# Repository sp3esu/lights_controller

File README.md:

# RC Light Controller

Wireless light controller for RC cars and trucks. A touchscreen handheld remote (TX) communicates over ESP-NOW with a receiver (RX) mounted on the vehicle to control multiple light outputs in real time.

## Translations

- [Polski (PL)](docs/README_PL.md)
- [Deutsch (DE)](docs/README_DE.md)
- [Francais (FR)](docs/README_FR.md)
- [Русский (RU)](docs/README_RU.md)
- [Українська (UA)](docs/README_UA.md)

## Features

- **5 independent light channels**: low beam, high beam, fog lights, light bar, hazard lights
- **Touchscreen UI**: 2x3 button grid on a 1.47" color display with LVGL
- **ESP-NOW wireless**: low-latency, connectionless protocol — no WiFi router needed
- **Automatic pairing**: one-button pairing with persistent NVS storage
- **Safety interlocks**: high beam requires low beam; failsafe shuts off all lights after 30s without signal
- **Connection monitoring**: heartbeats, ACK-based command confirmation, NeoPixel status LED
- **Test mode**: controller works standalone for UI testing without a receiver

## Hardware

### Controller (TX)

| Component | Details |
|-----------|---------|
| Board | [Waveshare ESP32-C6-Touch-LCD-1.47-M](https://www.waveshare.com/wiki/ESP32-C6-Touch-LCD-1.47) |
| MCU | ESP32-C6 (RISC-V, 8 MB flash) |
| Display | 1.47" JD9853, 172x320, rotated to 320x172 landscape |
| Touch | AXS5106L capacitive (I2C @ 0x63) |
| Status LED | WS2812 NeoPixel on GPIO8 |

### Receiver (RX)

| Component | Details |
|-----------|---------|
| Board | Any ESP32 dev board (classic Xtensa) |
| Light outputs | 5x GPIO, active-HIGH |
| Status LED | Built-in LED on GPIO2 |
| Pairing | BOOT button (GPIO0) — hold during power-up |

### Receiver Wiring

Connect ESP32 GPIOs to your lights through appropriate drivers (MOSFETs, relays, or LED drivers) depending on voltage and current requirements. All outputs are active-HIGH (3.3 V logic).

| GPIO | Function |
|------|----------|
| 16 | Fog lights |
| 17 | Low beam |
| 18 | High beam |
| 19 | Light bar |
| 21 | Hazard lights |
| 2 | Status LED |
| 0 | Pairing button (BOOT) |

## Building & Flashing

### Prerequisites

- [PlatformIO](https://platformio.org/) (CLI or IDE plugin)
- USB cables for both boards

### Build

```bash
# Build controller (TX) firmware
pio run -e controller

# Build receiver (RX) firmware
pio run -e receiver
```

### Flash

```bash
# Flash controller
pio run -e controller -t upload

# Flash receiver
pio run -e receiver -t upload
```

### Serial Monitor

```bash
pio device monitor    # 115200 baud
```

## Pairing

1. Power on the **receiver** while holding the **BOOT button** (GPIO0). The status LED flashes 3 times to confirm pairing mode.
2. On the **controller**, open **Settings** and tap **Start Pairing**.
3. Both devices exchange MAC addresses over ESP-NOW broadcast and store them in NVS.
4. Power-cycle both devices. The pairing is persistent and survives reboots.

## Protocol

Communication uses ESP-NOW with packed C structs (`__attribute__((packed))`) for cross-architecture compatibility (RISC-V controller / Xtensa receiver).

| Message | Direction | Purpose |
|---------|-----------|---------|
| `LightCommand` | TX -> RX | Set light state (5-bit bitmask) |
| `LightAck` | RX -> TX | Confirm current state |
| `Heartbeat` | RX -> TX | Keep-alive (every 2 s) |
| `StateReport` | RX -> TX | Full state + uptime |
| `PairRequest` | TX -> RX | Broadcast pairing request |
| `PairResponse` | RX -> TX | Pairing response with MAC |

### Light Bitmask

| Bit | Light |
|-----|-------|
| 0 | Fog lights |
| 1 | Low beam |
| 2 | High beam |
| 3 | Light bar |
| 4 | Hazard lights |

### Timing

| Parameter | Value |
|-----------|-------|
| ACK timeout | 200 ms |
| Max retries | 3 |
| Heartbeat interval | 2 s |
| Connection timeout (TX) | 6 s |
| Failsafe timeout (RX) | 30 s |

## Project Structure

```
light_controller/
├── src/
│   ├── controller/      # TX: display, touch, LVGL UI, ESP-NOW TX
│   └── receiver/        # RX: GPIO outputs, ESP-NOW RX, failsafe
├── lib/
│   ├── protocol/        # Shared wire protocol definitions
│   └── axs5106l_touch/  # AXS5106L touch driver
├── include/
│   └── lv_conf.h        # LVGL 8.4 configuration
└── platformio.ini       # Build configuration (two environments)
```

## Dependencies

### Controller
- [LVGL 8.4](https://lvgl.io/) — touchscreen UI framework
- [Arduino_GFX 1.6.5](https://github.com/moononournation/Arduino_GFX) — display driver
- [FastLED 3.9](https://fastled.io/) — NeoPixel status LED

### Receiver
- ESP-IDF built-ins only (ESP-NOW, WiFi, Preferences)

## License

This project is open source. See [LICENSE](LICENSE) for details.

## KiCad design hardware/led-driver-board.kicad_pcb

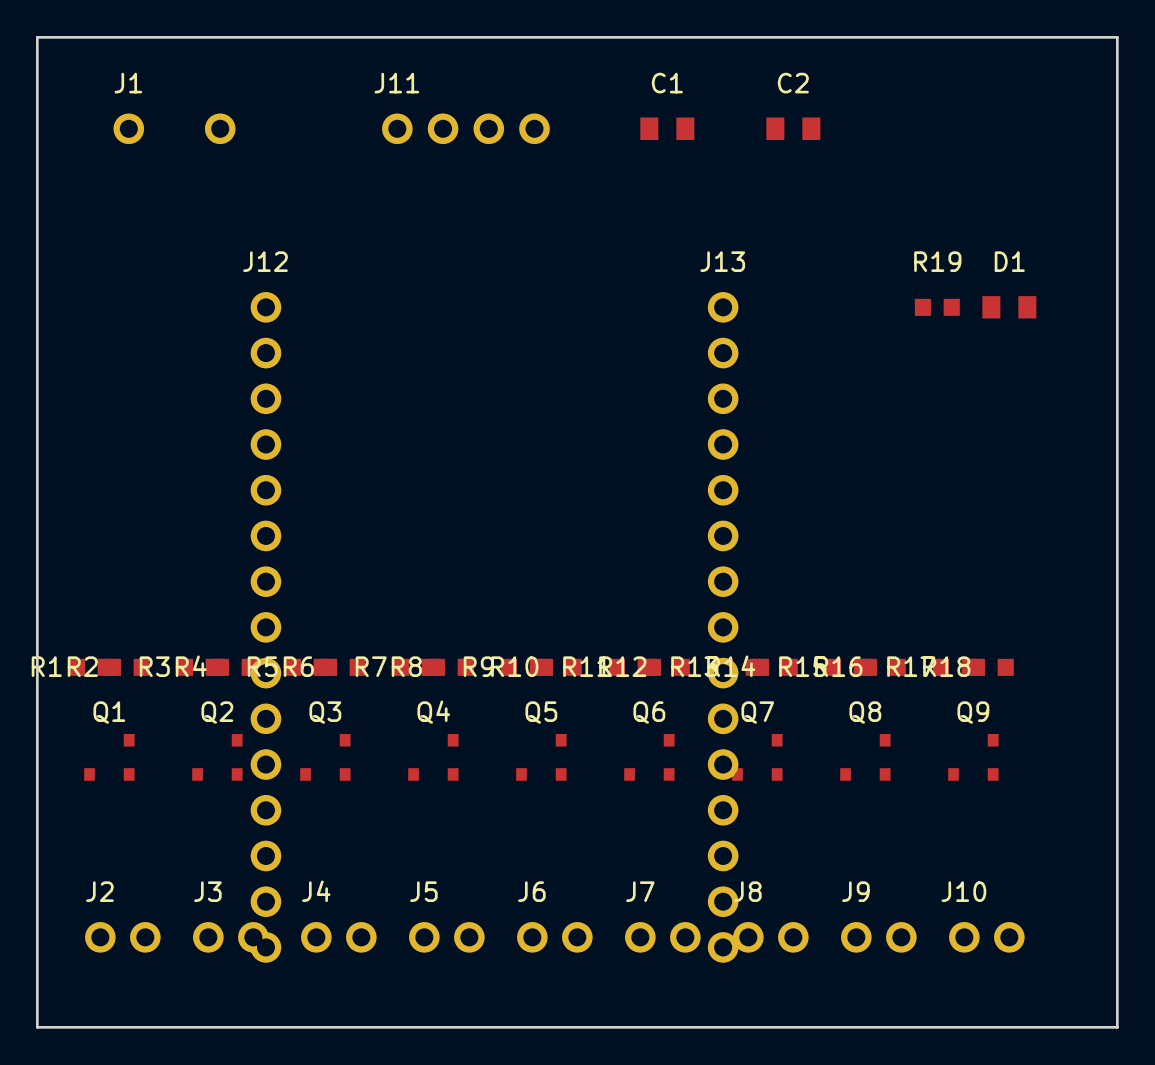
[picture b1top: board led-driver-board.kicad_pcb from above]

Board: 2 copper layers, 60.0 x 55.0 mm, 44 parts (0 on the bottom side), 22 nets, no tracks yet.

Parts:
C1, C2: 22uF; C_0805_2012Metric
D1: Green; LED_0805_2012Metric
J1: Battery; TerminalBlock_bornier-2_P5.08mm
J2: Ch1; JST_XH_B2B-XH-A_1x02_P2.50mm_Vertical
J3: Ch2; JST_XH_B2B-XH-A_1x02_P2.50mm_Vertical
J4: Ch3; JST_XH_B2B-XH-A_1x02_P2.50mm_Vertical
J5: Ch4; JST_XH_B2B-XH-A_1x02_P2.50mm_Vertical
J6: Ch5; JST_XH_B2B-XH-A_1x02_P2.50mm_Vertical
J7: Ch6; JST_XH_B2B-XH-A_1x02_P2.50mm_Vertical
J8: Ch7; JST_XH_B2B-XH-A_1x02_P2.50mm_Vertical
J9: Ch8; JST_XH_B2B-XH-A_1x02_P2.50mm_Vertical
J10: Ch9; JST_XH_B2B-XH-A_1x02_P2.50mm_Vertical
J11: MP1584EN; PinHeader_1x04_P2.54mm_Vertical
J12: ESP32_Left; PinSocket_1x15_P2.54mm_Vertical
J13: ESP32_Right; PinSocket_1x15_P2.54mm_Vertical
Q1, Q2, Q3, Q4, Q5, Q6, Q7, Q8, Q9: AO3400A; SOT-23
R1, R3, R5, R7, R9, R11, R13, R15, R17: 100; R_0603_1608Metric
R2, R4, R6, R8, R10, R12, R14, R16, R18: 10K; R_0603_1608Metric
R19: 1K; R_0603_1608Metric

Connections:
+5V: C2.1, J11.3
+BATT: C1.1, J1.1, J2.1, J3.1, J4.1, J5.1, J6.1, J7.1, J8.1, J9.1, J10.1, J11.1
DRAIN_1: J2.2, Q1.3
DRAIN_2: J3.2, Q2.3
DRAIN_3: J4.2, Q3.3
DRAIN_4: J5.2, Q4.3
DRAIN_5: J6.2, Q5.3
DRAIN_6: J7.2, Q6.3
DRAIN_7: J8.2, Q7.3
DRAIN_8: J9.2, Q8.3
DRAIN_9: J10.2, Q9.3
GATE_1: Q1.1, R1.2, R2.1
GATE_2: Q2.1, R3.2, R4.1
GATE_3: Q3.1, R5.2, R6.1
GATE_4: Q4.1, R7.2, R8.1
GATE_5: Q5.1, R9.2, R10.1
GATE_6: Q6.1, R11.2, R12.1
GATE_7: Q7.1, R13.2, R14.1
GATE_8: Q8.1, R15.2, R16.1
GATE_9: Q9.1, R17.2, R18.1
GND: C1.2, C2.2, D1.2, J1.2, J11.2, J11.4, Q1.2, Q2.2, Q3.2, Q4.2, Q5.2, Q6.2, Q7.2, Q8.2, Q9.2, R2.2, R4.2, R6.2, R8.2, R10.2, R12.2, R14.2, R16.2, R18.2
STATUS_LED: D1.1, R19.2

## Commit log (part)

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2026-02-10 added sidecar and td support
2026-02-10 added more files to git ignore
2026-02-10 PWM lights output
